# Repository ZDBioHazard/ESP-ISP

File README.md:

ESP-ISP
=======

This is just a simple programming jig for the ESP-12 module.

When putting this device together, use <=40-mil pogo pins for the ESP pins.
You can then place this device on top of a ESP-12 unit to access it's serial port.
(Be careful not to short any of the pogo pins on the metal can though. It can be tricky!)

* `P1` is normal FTDI header. 5V should work.
* `SW1` is a reset switch. Hold it down for >5s to bring `GPIO0` low and release to start flash mode.
* `D5` should light up when `GPIO0` is low.
* `D3` is a power indicator.
* `D2` should light up when the ESP is receiving serial data.

Check the schematic for the parts list.

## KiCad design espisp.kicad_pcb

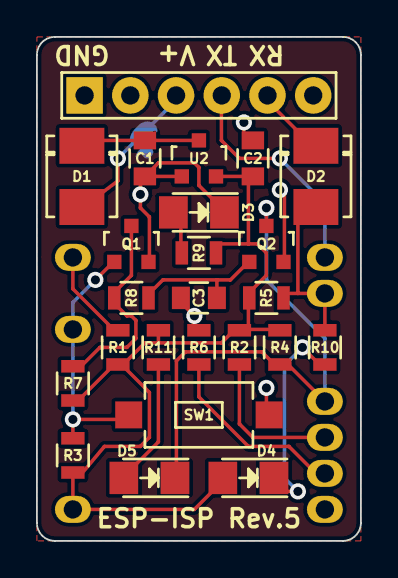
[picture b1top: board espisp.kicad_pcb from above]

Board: 2 copper layers, 18.0 x 28.0 mm, 25 parts (0 on the bottom side), 17 nets.

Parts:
C1, C2: 1uF; C_0805
C3: 2.2uF; C_0805
D1, D2: 1N5819; DO-214BA
D3, D4: GREEN; LED_1206
D5: RED; LED_1206
P1: FTDI_BASIC; Pin_Header_Simple_1x06
Q1, Q2: 2N7002; SOT-23
R1, R2, R3, R4, R5, R6: 10K; R_0805
R7, R8: 1M; R_0805
R9, R10, R11: 220; R_0805
SW1: RESET; SMD_PUSHBUTTON_3.6x6.0mm
U1: ESP-12; ESP-12-ISP
U2: XC6206; SOT-23

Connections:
+3V3: C2.1, D4.2, R1.1, R2.1, R3.2, R4.1, R5.2, R7.1, R9.2, R11.1, U1.8, U2.2
/CH_PD: Q1.1, R3.1, SW1.2, U1.3
/GPIO0: D5.1, Q2.3, R4.2, U1.12
/GPIO2: R2.2, U1.11
/GPIO15: R6.1, U1.10
/RESET: R1.2, U1.1
/RXD: D2.2, R5.1, R10.2, U1.15
/RXD_5V: D2.1, P1.5
/TXD: P1.4, U1.16
/VIN_5V: D1.2, P1.3
GND: C1.2, C2.2, C3.2, D3.1, P1.1, Q1.2, Q2.2, R6.2, SW1.1, U1.9, U2.1
unnamed: C1.1, D1.1, U2.3
unnamed: C3.1, Q2.1, R8.2
unnamed: D3.2, R9.1
unnamed: D4.1, R10.1
unnamed: D5.2, R11.2
unnamed: Q1.3, R7.2, R8.1

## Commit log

2016-06-15 Changed FLASH button to a general GPIO0 button.
    First manufacturing.
2016-07-28 Combine RESET and GPIO0 into one button. (Untested)
    Pressing the button should reset the MCU. Pressing and holding the
    button for ~5 seconds should make it enter flash mode upon release.
    Take a look at /proto/flash.txt to see it in action.
2016-08-05 Updated page layout.
2017-02-23 Update the schematic to use the new 'switches' library.
2017-02-23 Change the 41mil holes to 40mil holes.
2017-03-11 Placement tweaking and full reroute. (Rev. 5)
    * Moved the power LED near the power components.
    * All polarized components have the same orientation.
    * Extended the rim so the board can be held down easier.
    * Moved vias out from under components to make them easier to place.
2017-03-11 Added the gerber files and an image for reference.
2017-03-11 Add a basic README for GitHub.
